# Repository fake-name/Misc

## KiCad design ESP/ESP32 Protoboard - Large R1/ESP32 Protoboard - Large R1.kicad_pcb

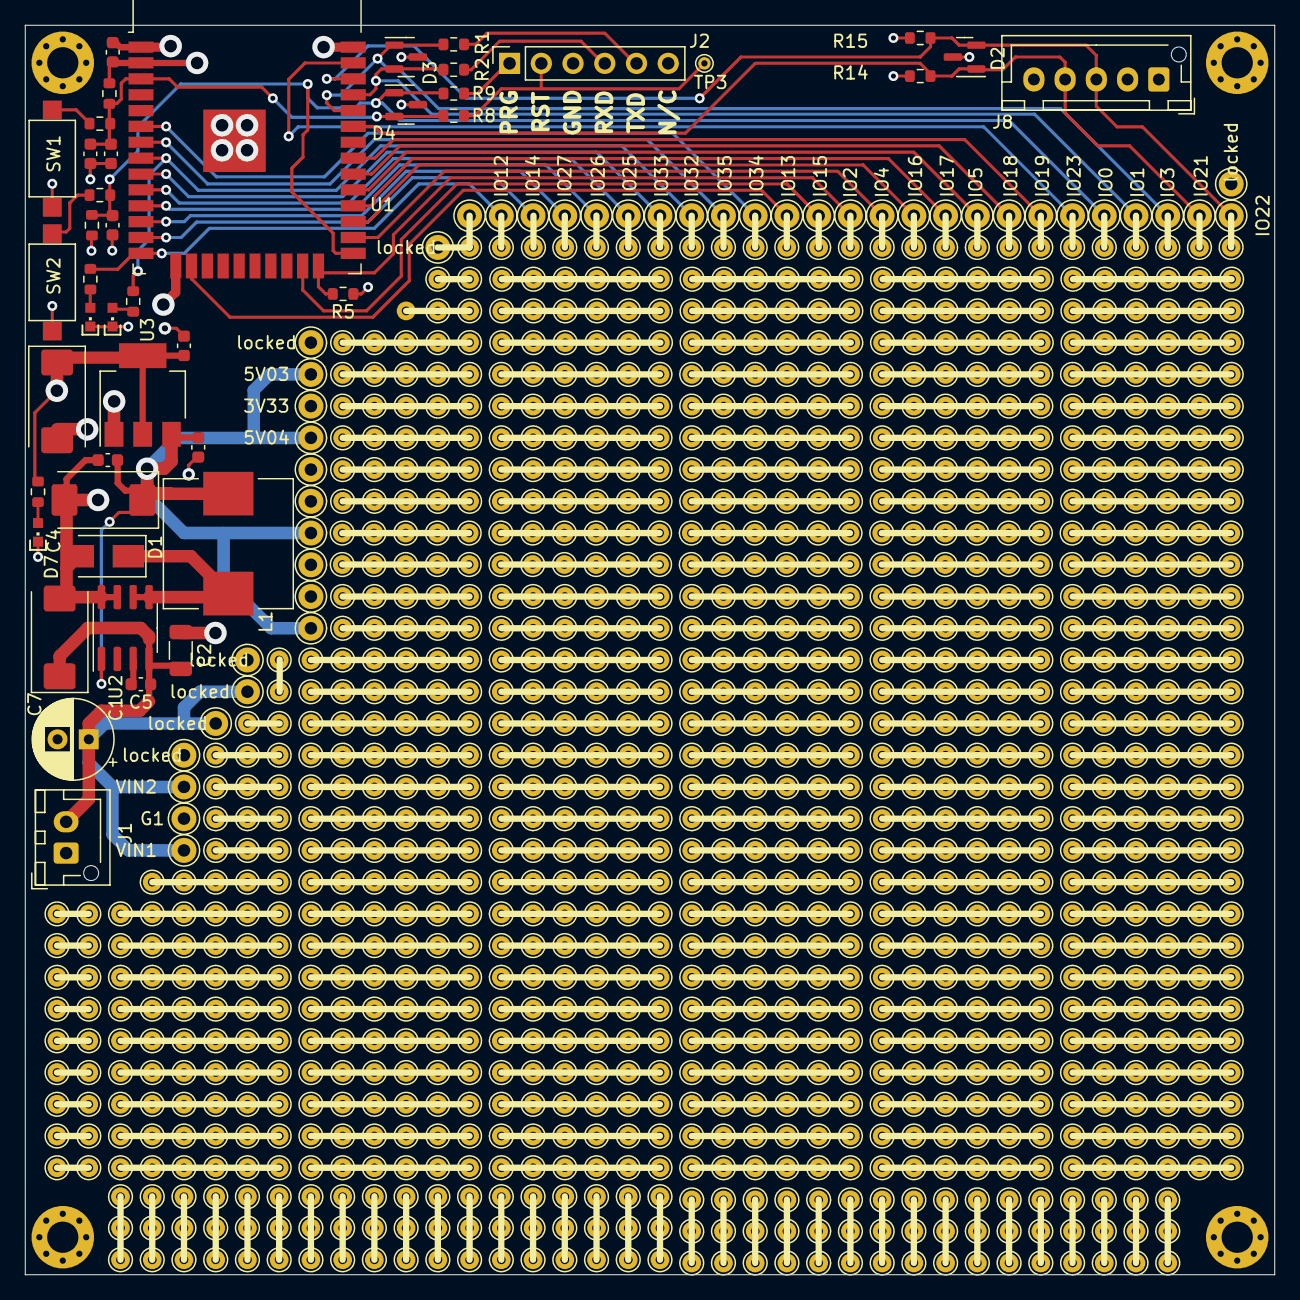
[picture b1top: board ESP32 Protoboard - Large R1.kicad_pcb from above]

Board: 4 copper layers, 100.0 x 100.0 mm, 92 parts (0 on the bottom side), 40 nets.

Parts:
3V33, 5V03, 5V04: TestPoint; Pin_D1.0mm_L10.0mm
C1: 47uF; CP_Radial_D6.3mm_P2.50mm
C2: 1 uF; C_1206_3216Metric
C3, C5, C6, C9, C11: 1 uF; C_0603_1608Metric
C4, C10: 100uF; CP_EIA-7343-20_Kemet-V
C7: 47uF; CP_EIA-7343-20_Kemet-V
C8: 0.1 uF; C_0603_1608Metric
C12, C13: DNP; C_0603_1608Metric
D1: SS36; D_SMA
D2, D3, D4: BAT54C; SOT-23
D7, D8, D12: LED; CHIPLED_0603
G1, G6: TestPoint; Pin_D1.0mm_L10.0mm
H1, H2, H3, H4: MountingHole; MountingHole_2.5mm_Pad_Via
IO0, IO1, IO2, IO3, IO4, IO5, IO12, IO13, IO14, IO15, IO16, IO17, IO18, IO19, IO21, IO22, IO23, IO25, IO26, IO27, IO32, IO33, IO34, IO35: TestPoint; Pin_D1.0mm_L10.0mm
J1: Conn_01x02; JST_XH_B2B-XH-AM_1x02_P2.50mm_Vertical
J2: Conn_01x06; PinSocket_1x06_P2.54mm_Vertical
J8: Conn_01x05; JST_XH_B5B-XH-AM_1x05_P2.50mm_Vertical
L1: 47uH/3A; L_Wuerth_HCI-1040
R1, R2, R3, R7, R8, R9, R10, R26, R27: 470R; R_0603_1608Metric
R4: 10K; R_0603_1608Metric
R5, R6, R14, R15: 4.7K; R_0603_1608Metric
SW1, SW2: SW_Push; SW_SPST_CK_RS282G05A3
TP3: TestPoint; TestPoint_THTPad_D1.0mm_Drill0.5mm
U1: ESP32-WROOM-32D; ESP32-WROOM-32
U2: XL2001; SOIC-8_3.9x4.9mm_P1.27mm
U3: AMS1117-3.3; SOT-223-3_TabPin2
VIN1, VIN2: TestPoint; Pin_D1.0mm_L10.0mm
locked: TestPoint; Pin_D1.0mm_L10.0mm
locked#2, locked#3, locked#4, locked#5, locked#6, locked#7, locked#8, locked#9, locked#10, locked#11, locked#12, locked#13: TestPoint; Pin_D1.0mm_L10.0mm

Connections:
+3V3: 3V33.1, C9.1, C10.1, C11.1, D2.3 (A), D3.3 (A), D4.3 (A), J8.2, R4.2, R6.2, R14.2, R15.2, R26.2, U1.2 (VDD), U3.2 (VO), locked#2.1, locked#10.1, locked#12.1
+5V: 5V03.1, 5V04.1, C3.1, C4.1, C6.1, J8.1, L1.2, U2.1 (FB), U3.3 (VI), locked#3.1, locked#13.1
/PROG: C13.1, D4.1 (K), IO0.1, R6.1, R7.2, R9.1, U1.25 (IO0)
/RESET: C8.1, C12.1, D4.2 (K), R3.2, R4.1, R8.1, U1.3 (EN)
/RXD: D3.2 (K), IO1.1, R2.1, U1.35 (TXD0/IO1)
/TXD: D3.1 (K), IO3.1, R1.1, U1.34 (RXD0/IO3)
GND: C1.2, C2.2, C3.2, C4.2, C6.2, C7.2, C8.2, C9.2, C10.2, C11.2, C12.2, C13.2, D1.2 (A), D7.1 (K), D8.1 (K), D12.1 (K), G1.1, G6.1, J1.1, J2.3, J8.5, R5.1, SW1.2, SW2.2, U1.1 (GND), U1.15 (GND), U1.38 (GND), U1.39 (GND), U2.7 (GND), U2.8 (GND), U3.1 (GND), locked#4.1, locked#5.1, locked#6.1, locked#7.1, locked#9.1, locked#11.1
unnamed: C5.2, U2.3 (VC)
unnamed: D1.1 (K), L1.1, U2.5 (SW), U2.6 (SW)
unnamed: D2.1 (K), IO21.1, J8.4, R14.1, U1.33 (IO21)
unnamed: D2.2 (K), IO22.1, J8.3, R15.1, U1.36 (IO22)
unnamed: D7.2 (A), R26.1
unnamed: D8.2 (A), R27.1
unnamed: D12.2 (A), R10.1
unnamed: IO2.1, R5.2, U1.24 (IO2)
unnamed: IO4.1, U1.26 (IO4)
unnamed: IO5.1, U1.29 (IO5)
unnamed: IO12.1, R10.2, U1.14 (IO12)
unnamed: IO13.1, U1.16 (IO13)
unnamed: IO14.1, U1.13 (IO14)
unnamed: IO15.1, U1.23 (IO15)
unnamed: IO16.1, U1.27 (IO16)
unnamed: IO17.1, U1.28 (IO17)
unnamed: IO18.1, U1.30 (IO18)
unnamed: IO19.1, U1.31 (IO19)
unnamed: IO23.1, U1.37 (IO23)
unnamed: IO25.1, U1.10 (IO25)
unnamed: IO26.1, U1.11 (IO26)
unnamed: IO27.1, U1.12 (IO27)
unnamed: IO32.1, R27.2, U1.8 (IO32)
unnamed: IO33.1, U1.9 (IO33)
unnamed: IO34.1, U1.6 (IO34)
unnamed: IO35.1, U1.7 (IO35)
unnamed: J2.1, R9.2
unnamed: J2.2, R8.2, TP3.1
unnamed: J2.4, R2.2
unnamed: J2.5, R1.2
unnamed: R3.1, SW1.1
unnamed: R7.1, SW2.1
VCC: C1.1, C2.1, C5.1, C7.1, J1.2, U2.4 (VIn), VIN1.1, VIN2.1, locked.1, locked#8.1

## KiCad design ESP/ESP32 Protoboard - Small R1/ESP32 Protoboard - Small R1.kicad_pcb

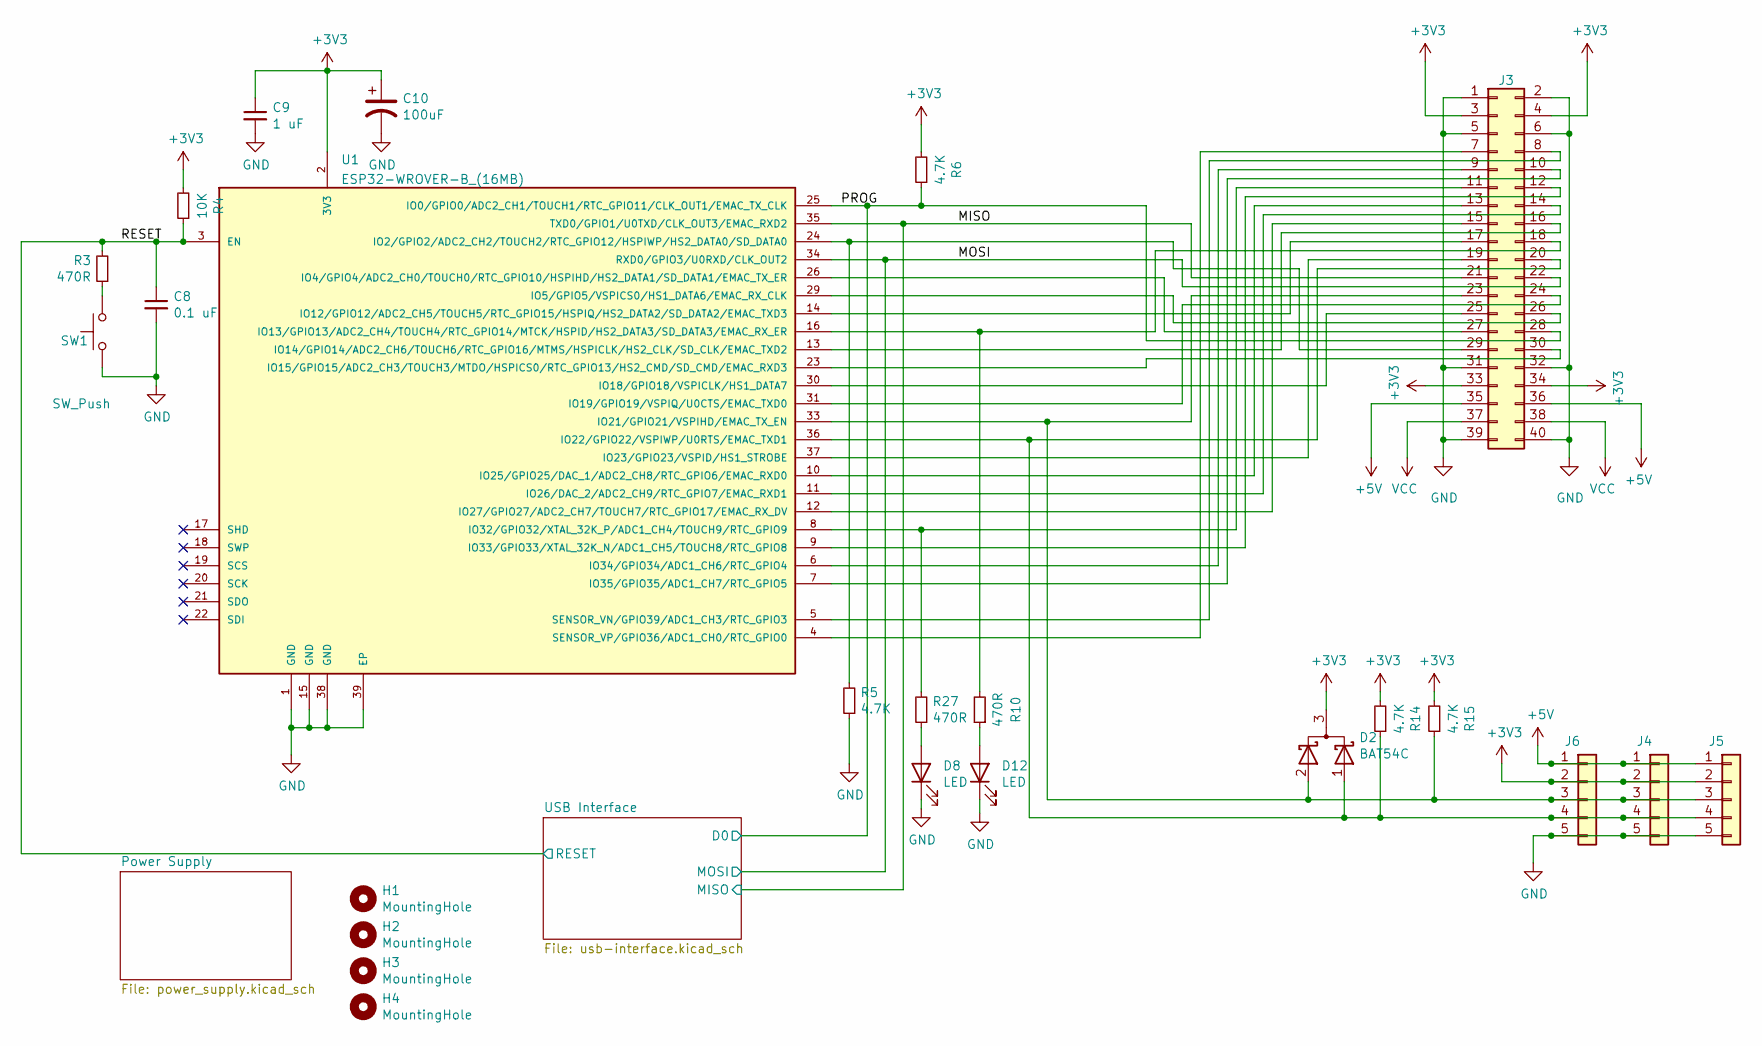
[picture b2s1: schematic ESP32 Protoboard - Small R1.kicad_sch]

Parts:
C8: 0.1 uF; C_0603_1608Metric; LCSC C15849
C9: 1 uF; C_0603_1608Metric; LCSC C14663
C10: 100uF; CP_EIA-7343-20_Kemet-V; LCSC C14663
D2: BAT54C; SOT-23; LCSC C14663
D8, D12: LED; CHIPLED_0603; LCSC C14663
H1, H2, H3, H4: MountingHole; MountingHole_2.5mm_Pad_Via
J3: Conn_02x20_Top_Bottom; PinHeader_2x20_P2.54mm_Vertical
J4, J5, J6: Conn_01x05; JST_XH_B5B-XH-AM_1x05_P2.50mm_Vertical; LCSC C14663
R3, R10, R27: 470R; R_0603_1608Metric; LCSC C14663
R4: 10K; R_0603_1608Metric; LCSC C14663
R5, R6, R14, R15: 4.7K; R_0603_1608Metric; LCSC C14663
SW1: SW_Push; SW_SPST_CK_RS282G05A3; LCSC C14663
U1: ESP32-WROVER-B_(16MB); XCVR_ESP32-WROVER-B_(16MB); PARTREV 1.1

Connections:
+3V3: C9.1, C10.1, D2.3 (A), J3.3, J3.4, J3.33, J3.34, J4.2, J5.2, J6.2, R4.2, R6.2, R14.2, R15.2, U1.2 (3V3); also elsewhere on the board
+5V: J3.35, J3.36, J4.1, J5.1, J6.1; also elsewhere on the board
/MISO: J3.21, U1.35 (TXD0/GPIO1/U0TXD/CLK_OUT3/EMAC_RXD2); also elsewhere on the board
/MOSI: J3.22, U1.34 (RXD0/GPIO3/U0RXD/CLK_OUT2); also elsewhere on the board
/PROG: J3.28, R6.1, U1.25 (IO0/GPIO0/ADC2_CH1/TOUCH1/RTC_GPIO11/CL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); also elsewhere on the board
/RESET: C8.1, R3.2, R4.1, U1.3 (EN); also elsewhere on the board
GND: C8.2, C9.2, C10.2, D8.1 (K), D12.1 (K), J3.1, J3.2, J3.5, J3.6, J3.31, J3.32, J3.39, J3.40, J4.5, J5.5, J6.5, R5.1, SW1.2, U1.1 (GND), U1.15 (GND), U1.38 (GND), U1.39 (EP); also elsewhere on the board
unnamed: D2.1 (K), J3.20, J4.4, J5.4, J6.4, R14.1, U1.36 (IO22/GPIO22/VSPIWP/U0RTS/EMAC_TXD1)
unnamed: D2.2 (K), J3.23, J4.3, J5.3, J6.3, R15.1, U1.33 (IO21/GPIO21/VSPIHD/EMAC_TX_EN)
unnamed: D8.2 (A), R27.1
unnamed: D12.2 (A), R10.1
unnamed: J3.7, U1.4 (SENSOR_VP/GPIO36/ADC1_CH0/RTC_GPIO0)
unnamed: J3.8, U1.5 (SENSOR_VN/GPIO39/ADC1_CH3/RTC_GPIO3)
unnamed: J3.9, U1.6 (IO34/GPIO34/ADC1_CH6/RTC_GPIO4)
unnamed: J3.10, U1.7 (IO35/GPIO35/ADC1_CH7/RTC_GPIO5)
unnamed: J3.11, R27.2, U1.8 (IO32/GPIO32/XTAL_32K_P/ADC1_CH4/TOUCH9/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)
unnamed: J3.12, U1.9 (IO33/GPIO33/XTAL_32K_N/ADC1_CH5/TOUCH8/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)
unnamed: J3.13, U1.10 (IO25/GPIO25/DAC_1/ADC2_CH8/RTC_GPIO6/EM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)
unnamed: J3.14, U1.11 (IO26/DAC_2/ADC2_CH9/RTC_GPIO7/EMAC_RXD1)
unnamed: J3.15, U1.12 (IO27/GPIO27/ADC2_CH7/TOUCH7/RTC_GPIO17/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)
unnamed: J3.16, U1.13 (IO14/GPIO14/ADC2_CH6/TOUCH6/RTC_GPIO16/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)
unnamed: J3.17, U1.14 (IO12/GPIO12/ADC2_CH5/TOUCH5/RTC_GPIO15/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)
unnamed: J3.18, R10.2, U1.16 (IO13/GPIO13/ADC2_CH4/TOUCH4/RTC_GPIO14/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)
unnamed: J3.19, U1.37 (IO23/GPIO23/VSPID/HS1_STROBE)
unnamed: J3.24, U1.31 (IO19/GPIO19/VSPIQ/U0CTS/EMAC_TXD0)
unnamed: J3.25, U1.30 (IO18/GPIO18/VSPICLK/HS1_DATA7)
unnamed: J3.26, U1.29 (IO5/GPIO5/VSPICS0/HS1_DATA6/EMAC_RX_CLK)
unnamed: J3.27, U1.26 (IO4/GPIO4/ADC2_CH0/TOUCH0/RTC_GPIO10/HS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)
unnamed: J3.29, R5.2, U1.24 (IO2/GPIO2/ADC2_CH2/TOUCH2/RTC_GPIO12/HS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)
unnamed: J3.30, U1.23 (IO15/GPIO15/ADC2_CH3/TOUCH3/MTDO/HSPICS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)
unnamed: R3.1, SW1.1
VCC: J3.37, J3.38; also elsewhere on the board

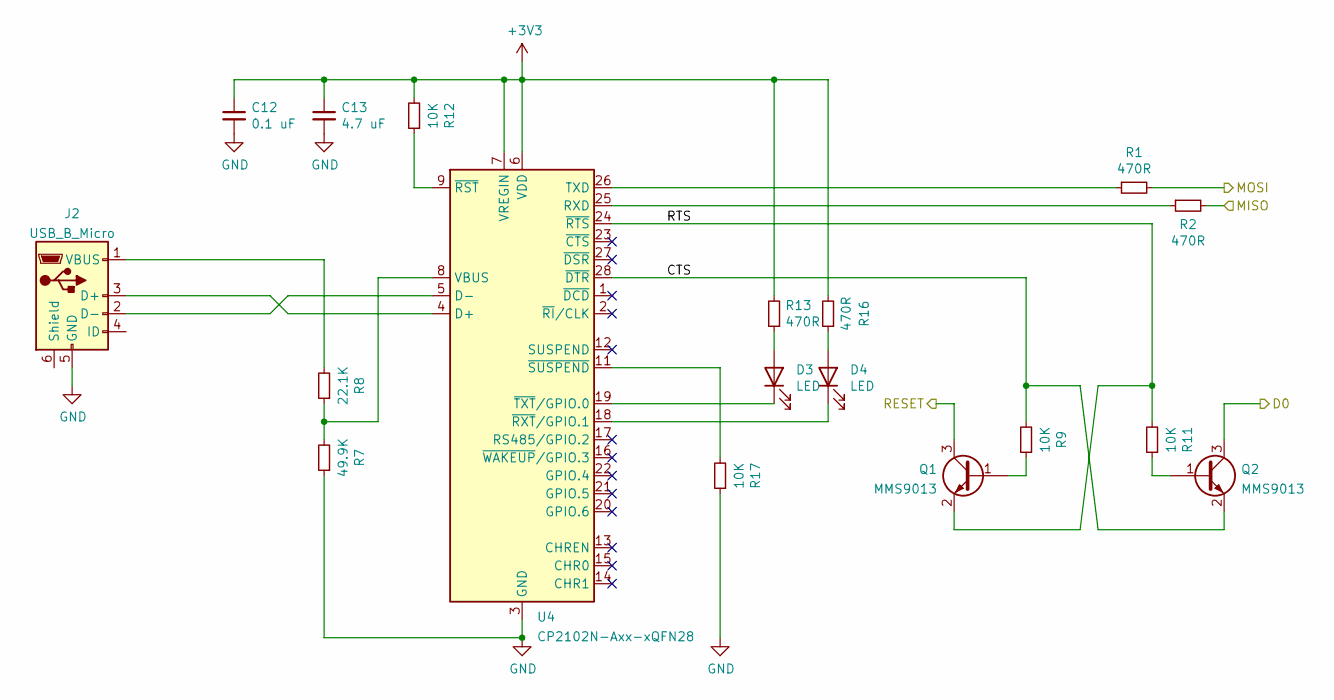
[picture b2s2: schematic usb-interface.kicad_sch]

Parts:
C12: 0.1 uF; C_0603_1608Metric; LCSC C14663
C13: 4.7 uF; C_0603_1608Metric; LCSC C19666
D3, D4: LED; CHIPLED_0603; LCSC C14663
J2: USB_B_Micro; Molex--0-0-0
Q1, Q2: MMS9013; SOT-23; LCSC MMS9013
R1, R2, R13, R16: 470R; R_0603_1608Metric; LCSC C14663
R7: 49.9K; R_0603_1608Metric; LCSC C23184
R8: 22.1K; R_0603_1608Metric; LCSC C23184
R9, R11, R12, R17: 10K; R_0603_1608Metric; LCSC C25804
U4: CP2102N-Axx-xQFN28; QFN-28-1EP_5x5mm_P0.5mm_EP3.35x3.35mm

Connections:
+3V3: C12.1, C13.1, R12.2, R13.2, R16.2, U4.6 (VDD), U4.7 (VREGIN); also elsewhere on the board
/MISO: R2.2; also elsewhere on the board
/MOSI: R1.2; also elsewhere on the board
/PROG: Q2.3 (C); also elsewhere on the board
/RESET: Q1.3 (C); also elsewhere on the board
/USB Interface/CTS: Q2.2 (E), R9.2, U4.28 (~DTR)
/USB Interface/RTS: Q1.2 (E), R11.2, U4.24 (~RTS)
GND: C12.2, C13.2, J2.5 (GND), R7.1, R17.1, U4.3 (GND), U4.29 (GND); also elsewhere on the board
unnamed: D3.1 (K), U4.19 (~TXT/GPIO.0)
unnamed: D3.2 (A), R13.1
unnamed: D4.1 (K), U4.18 (~RXT/GPIO.1)
unnamed: D4.2 (A), R16.1
unnamed: J2.1 (VBUS), R8.2
unnamed: J2.2 (D-), U4.5 (D-)
unnamed: J2.3 (D+), U4.4 (D+)
unnamed: Q1.1 (B), R9.1
unnamed: Q2.1 (B), R11.1
unnamed: R1.1, U4.26 (TXD)
unnamed: R2.1, U4.25 (RXD)
unnamed: R7.2, R8.1, U4.8 (VBUS)
unnamed: R12.1, U4.9 (~RST)
unnamed: R17.2, U4.11 (~SUSPEND)

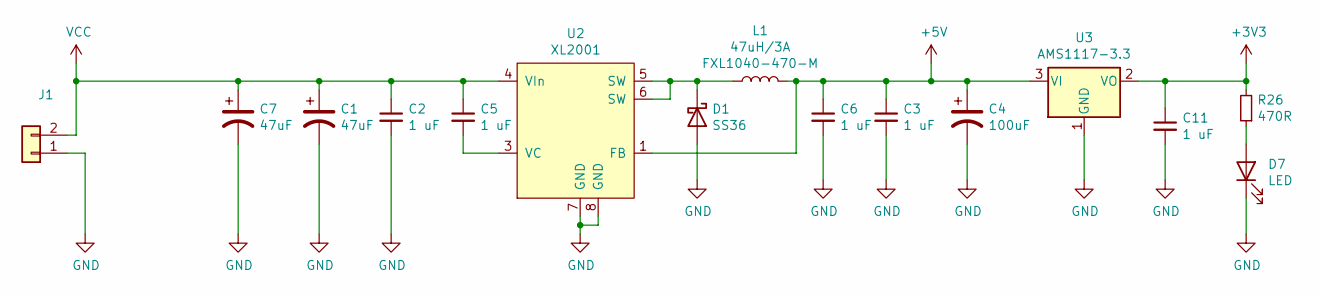
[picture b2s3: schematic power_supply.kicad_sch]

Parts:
C1: 47uF; CP_Radial_D6.3mm_P2.50mm; LCSC C14663
C2: 1 uF; C_1206_3216Metric; LCSC C14663
C3, C5, C6, C11: 1 uF; C_0603_1608Metric; LCSC C14663
C4: 100uF; CP_EIA-7343-20_Kemet-V; LCSC C14663
C7: 47uF; CP_EIA-7343-20_Kemet-V; LCSC C14663
D1: SS36; D_SMA; LCSC C14663
D7: LED; CHIPLED_0603; LCSC C14663
J1: Conn_01x02; JST_XH_B2B-XH-AM_1x02_P2.50mm_Vertical; LCSC C14663
L1: 47uH/3A; L_Wuerth_HCI-1040; LCSC C14663
R26: 470R; R_0603_1608Metric; LCSC C14663
U2: XL2001; SOIC-8_3.9x4.9mm_P1.27mm; LCSC C14663
U3: AMS1117-3.3; SOT-223-3_TabPin2; LCSC C14663

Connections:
+3V3: C11.1, R26.2, U3.2 (VO); also elsewhere on the board
+5V: C3.1, C4.1, C6.1, L1.2, U2.1 (FB), U3.3 (VI); also elsewhere on the board
GND: C1.2, C2.2, C3.2, C4.2, C6.2, C7.2, C11.2, D1.2 (A), D7.1 (K), J1.1, U2.7 (GND), U2.8 (GND), U3.1 (GND); also elsewhere on the board
unnamed: C5.2, U2.3 (VC)
unnamed: D1.1 (K), L1.1, U2.5 (SW), U2.6 (SW)
unnamed: D7.2 (A), R26.1
VCC: C1.1, C2.1, C5.1, C7.1, J1.2, U2.4 (VIn); also elsewhere on the board

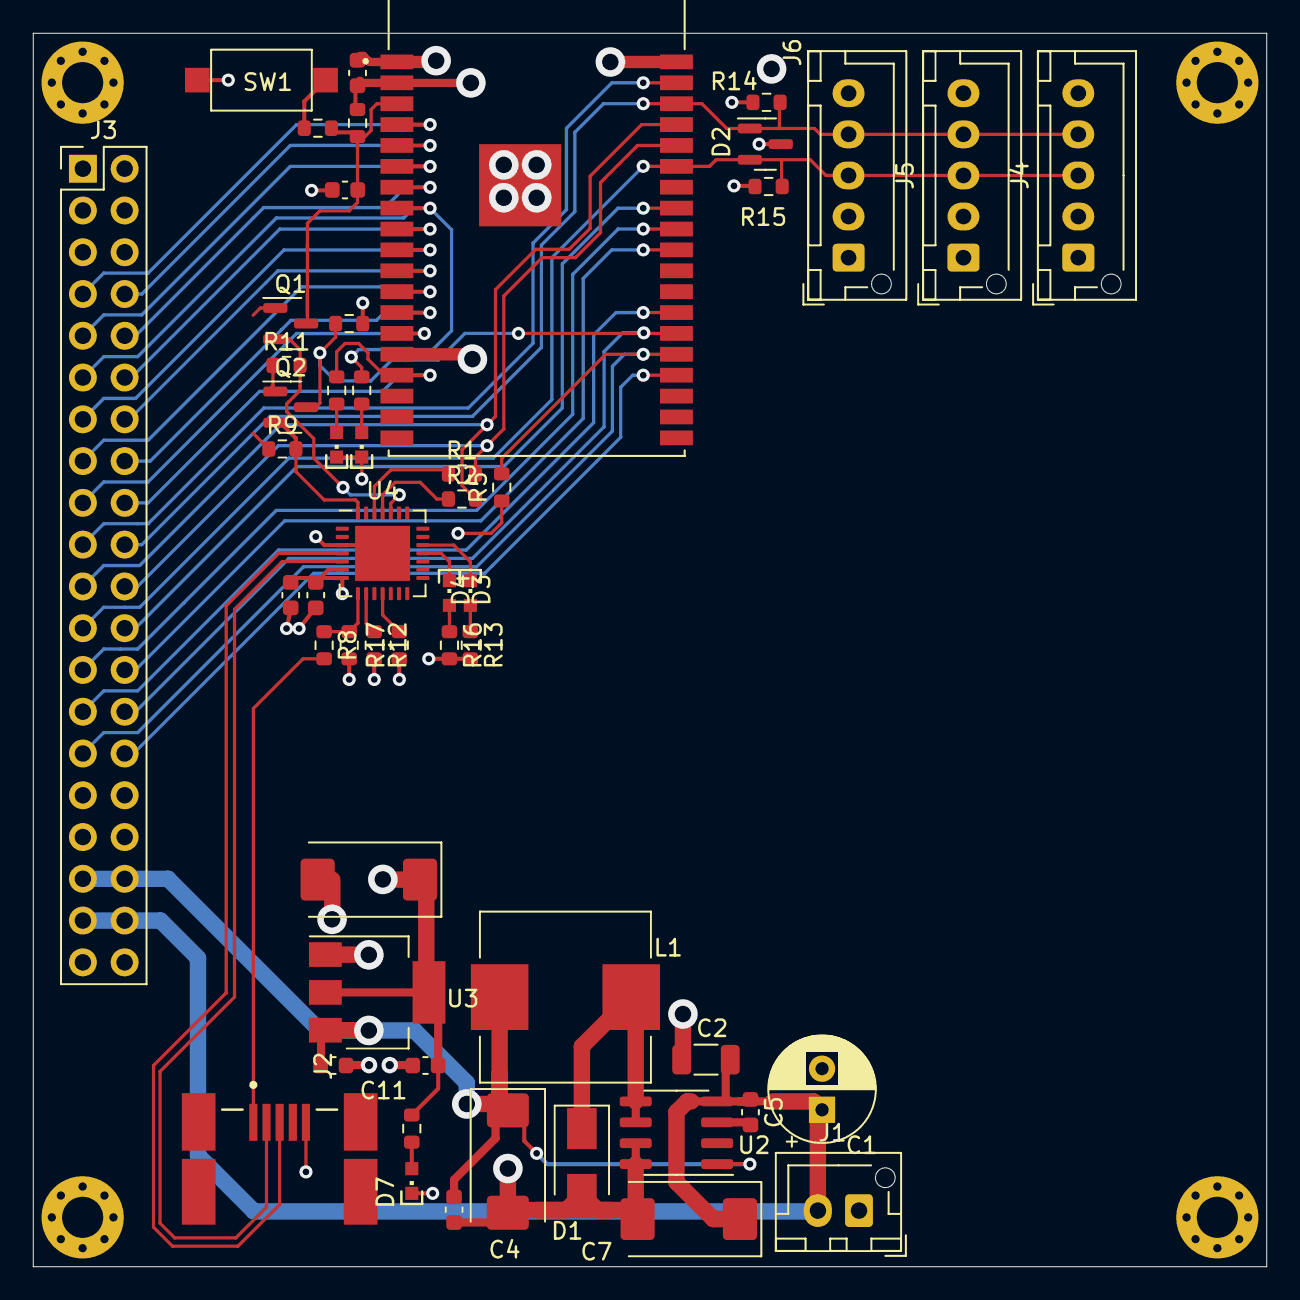
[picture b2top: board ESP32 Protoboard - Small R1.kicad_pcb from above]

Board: 4 copper layers, 75.0 x 75.0 mm, 57 parts (0 on the bottom side), 51 nets.

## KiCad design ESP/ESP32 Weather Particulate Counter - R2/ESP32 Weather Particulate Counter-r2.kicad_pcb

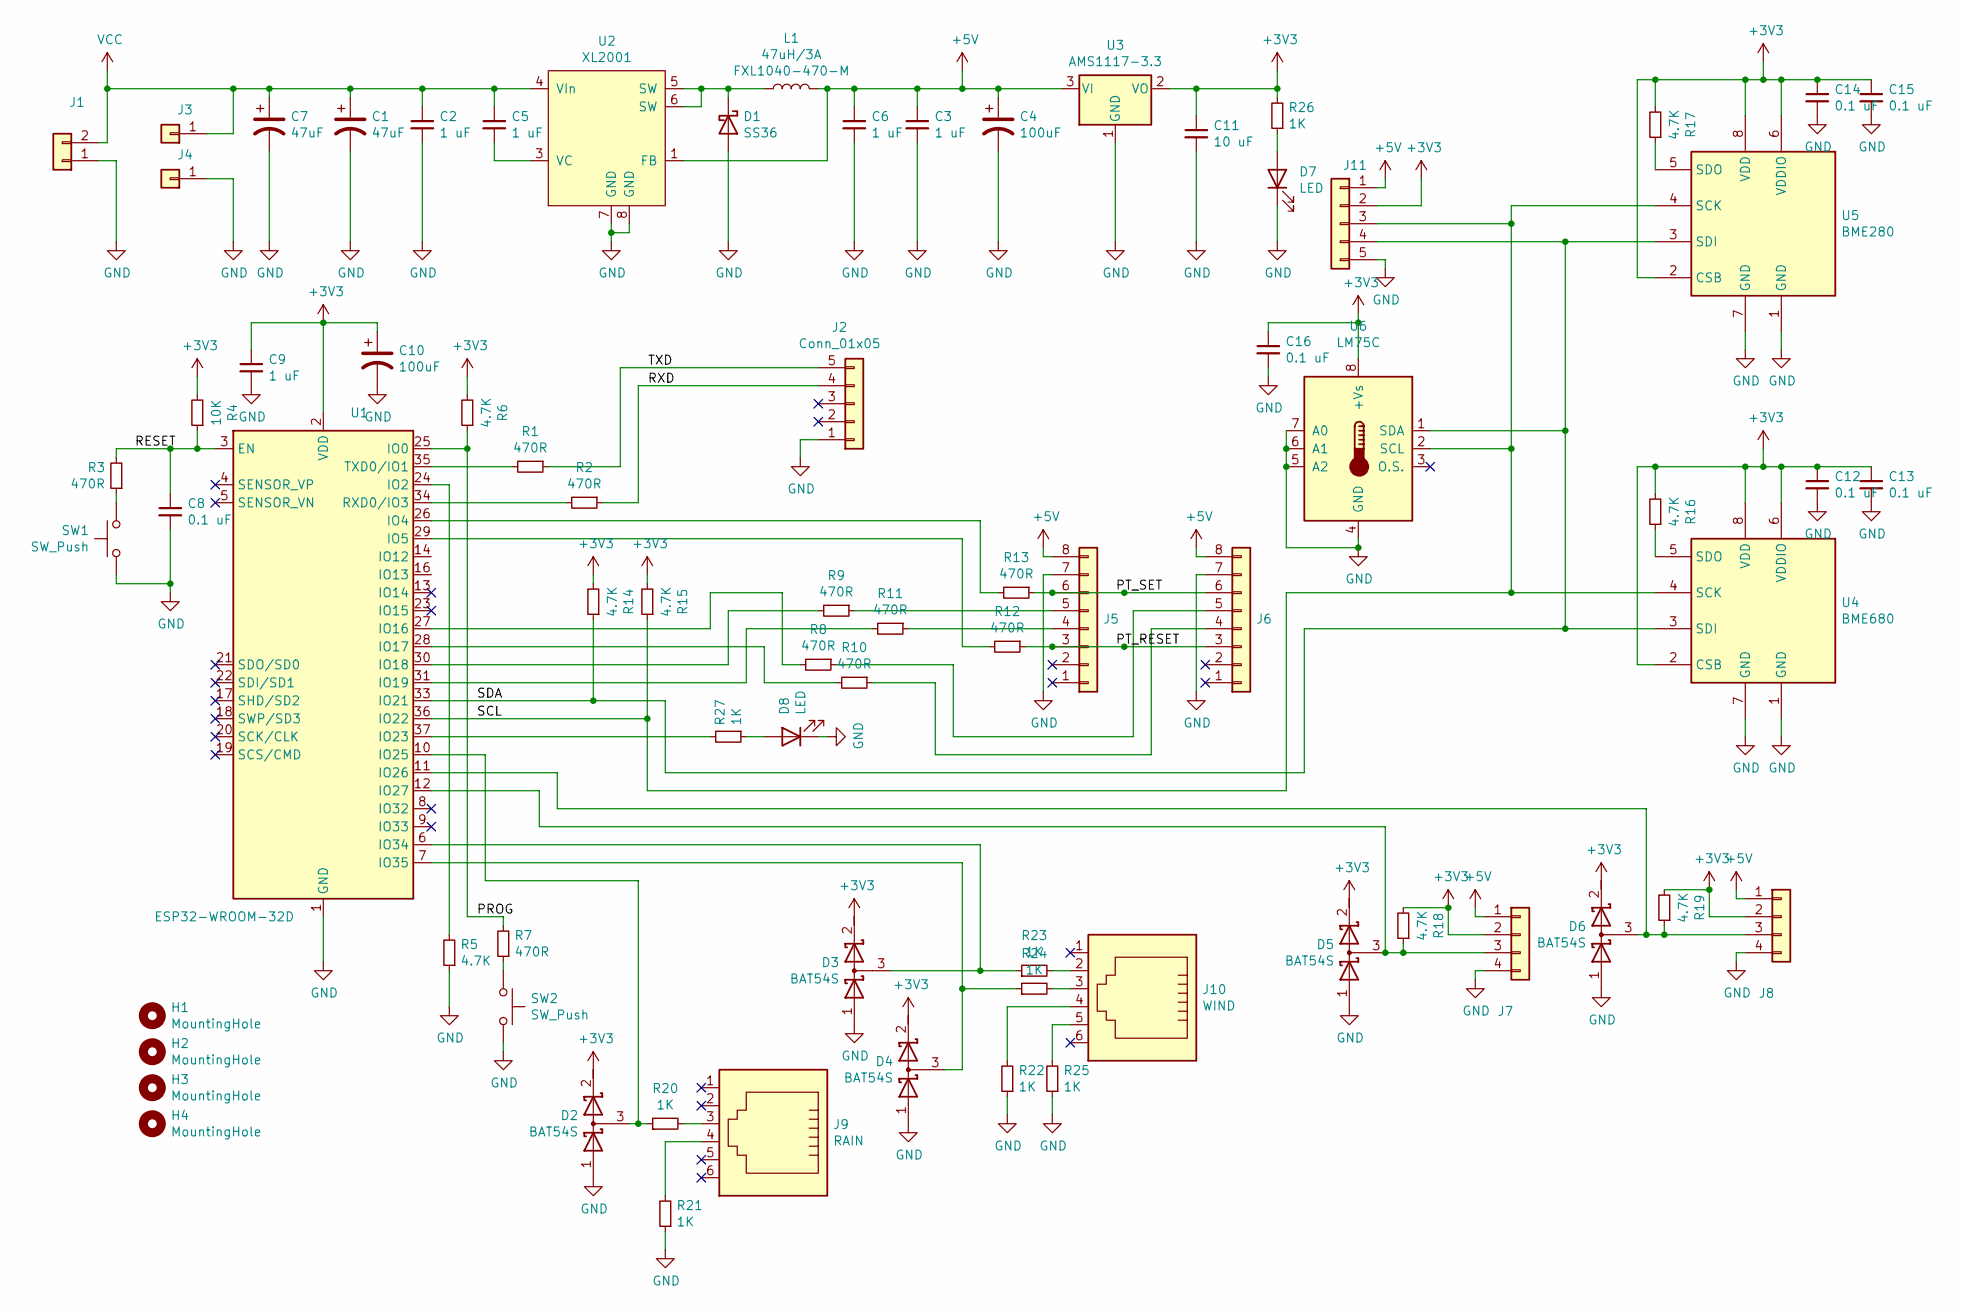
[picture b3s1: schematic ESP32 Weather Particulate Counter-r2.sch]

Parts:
C1: 47uF; CP_Radial_D6.3mm_P2.50mm
C2: 1 uF; C_1206_3216Metric_Pad1.42x1.75mm_HandSolder
C3, C5, C6, C9: 1 uF; C_0603_1608Metric_Pad1.05x0.95mm_HandSolder
C4, C10: 100uF; CP_EIA-7343-20_Kemet-V_Pad2.25x2.55mm_HandSolder
C7: 47uF; CP_EIA-7343-20_Kemet-V_Pad2.25x2.55mm_HandSolder
C8, C12, C13, C14, C15, C16: 0.1 uF; C_0603_1608Metric_Pad1.05x0.95mm_HandSolder
C11: 10 uF; C_0603_1608Metric_Pad1.05x0.95mm_HandSolder
D1: SS36; D_SMA_Handsoldering
D2, D3, D4, D5, D6: BAT54S; SOT-23
D7, D8: LED; CHIPLED_0603
H1, H2, H3, H4: MountingHole; MountingHole_2.5mm_Pad_Via
J1: Conn_01x02; PinHeader_1x02_P2.54mm_Vertical
J2: Conn_01x05; PinHeader_1x05_P2.54mm_Vertical
J3, J4: Conn_01x01; Pin_D1.3mm_L11.0mm
J5, J6: Conn_01x08; Molex_PicoBlade_53047-0810_1x08_P1.25mm_Vertical
J7, J8: Conn_01x04; JST_XH_B4B-XH-AM_1x04_P2.50mm_Vertical
J9: RAIN; RJ25_Wayconn_MJEA-660X1_Horizontal
J10: WIND; RJ25_Wayconn_MJEA-660X1_Horizontal
J11: Conn_01x05; JST_XH_B5B-XH-AM_1x05_P2.50mm_Vertical
L1: 47uH/3A; L_Wuerth_HCI-1040
R1, R2, R3, R7, R8, R9, R10, R11, R12, R13: 470R; R_0603_1608Metric_Pad1.05x0.95mm_HandSolder
R4: 10K; R_0603_1608Metric_Pad1.05x0.95mm_HandSolder
R5, R6, R14, R15, R16, R17, R18, R19: 4.7K; R_0603_1608Metric_Pad1.05x0.95mm_HandSolder
R20, R21, R22, R23, R24, R25, R26, R27: 1K; R_0603_1608Metric_Pad1.05x0.95mm_HandSolder
SW1, SW2: SW_Push; K2-1823SA-A4DW-06
U1: ESP32-WROOM-32D; ESP32-WROOM-32
U2: XL2001; SOIC-8_3.9x4.9mm_P1.27mm
U3: AMS1117-3.3; SOT-223-3_TabPin2
U4: BME680; Bosch_LGA-8_3x3mm_P0.8mm_ClockwisePinNumbering
U5: BME280; Bosch_LGA-8_2.5x2.5mm_P0.65mm_ClockwisePinNumbering
U6: LM75C; MSOP-8_3x3mm_P0.65mm

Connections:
+3V3: C9.1, C10.1, C11.1, C12.1, C13.1, C14.1, C15.1, C16.1, D2.2 (K), D3.2 (K), D4.2 (K), D5.2 (K), D6.2 (K), J7.2, J8.2, J11.2, R4.2, R6.2, R14.2, R15.2, R16.2, R17.2, R18.2, R19.2, R26.2, U1.2 (VDD), U3.2 (VO), U4.2 (CSB), U4.6 (VDDIO), U4.8 (VDD), U5.2 (CSB), U5.6 (VDDIO), U5.8 (VDD), U6.8 (+Vs)
+5V: C3.1, C4.1, C6.1, J5.8, J6.8, J7.1, J8.1, J11.1, L1.2, U2.1 (FB), U3.3 (VI)
/PROG: R6.1, R7.2, U1.25 (IO0)
/PT_RESET: J5.3, J6.3, R12.1
/PT_SET: J5.6, J6.6, R13.1
/RESET: C8.1, R3.2, R4.1, U1.3 (EN)
/RXD: J2.4, R2.1
/SCL: J11.3, R15.1, U1.36 (IO22), U4.4 (SCK), U5.4 (SCK), U6.2 (SCL)
/SDA: J11.4, R14.1, U1.33 (IO21), U4.3 (SDI), U5.3 (SDI), U6.1 (SDA)
/TXD: J2.5, R1.1
GND: C1.2, C2.2, C3.2, C4.2, C6.2, C7.2, C8.2, C9.2, C10.2, C11.2, C12.2, C13.2, C14.2, C15.2, C16.2, D1.2 (A), D2.1 (A), D3.1 (A), D4.1 (A), D5.1 (A), D6.1 (A), D7.1 (K), D8.1 (K), J1.1, J2.1, J4.1, J5.7, J6.7, J7.4, J8.4, J11.5, R5.1, R21.1, R22.1, R25.1, SW1.2, SW2.2, U1.1 (GND), U1.15 (GND), U1.38 (GND), U1.39 (GND), U2.7 (GND), U2.8 (GND), U3.1 (GND), U4.1 (GND), U4.7 (GND), U5.1 (GND), U5.7 (GND), U6.4 (GND), U6.5 (A2), U6.6 (A1), U6.7 (A0)
unnamed: C5.2, U2.3 (VC)
unnamed: D1.1 (K), L1.1, U2.5 (SW), U2.6 (SW)
unnamed: D2.3 (common), R20.1, U1.10 (IO25)
unnamed: D3.3 (common), R23.1, U1.6 (IO34)
unnamed: D4.3 (common), R24.1, U1.7 (IO35)
unnamed: D5.3 (common), J7.3, R18.1, U1.12 (IO27)
unnamed: D6.3 (common), J8.3, R19.1, U1.11 (IO26)
unnamed: D7.2 (A), R26.1
unnamed: D8.2 (A), R27.1
unnamed: J5.4, R11.1
unnamed: J5.5, R9.1
unnamed: J6.4, R10.1
unnamed: J6.5, R8.1
unnamed: J9.3, R20.2
unnamed: J9.4, R21.2
unnamed: J10.2, R23.2
unnamed: J10.3, R24.2
unnamed: J10.4, R22.2
unnamed: J10.5, R25.2
unnamed: R1.2, U1.35 (TXD0/IO1)
unnamed: R2.2, U1.34 (RXD0/IO3)
unnamed: R3.1, SW1.1
unnamed: R5.2, U1.24 (IO2)
unnamed: R7.1, SW2.1
unnamed: R8.2, U1.27 (IO16)
unnamed: R9.2, U1.30 (IO18)
unnamed: R10.2, U1.28 (IO17)
unnamed: R11.2, U1.31 (IO19)
unnamed: R12.2, U1.29 (IO5)
unnamed: R13.2, U1.26 (IO4)
unnamed: R16.1, U4.5 (SDO)
unnamed: R17.1, U5.5 (SDO)
unnamed: R27.2, U1.37 (IO23)
VCC: C1.1, C2.1, C5.1, C7.1, J1.2, J3.1, U2.4 (VIn)

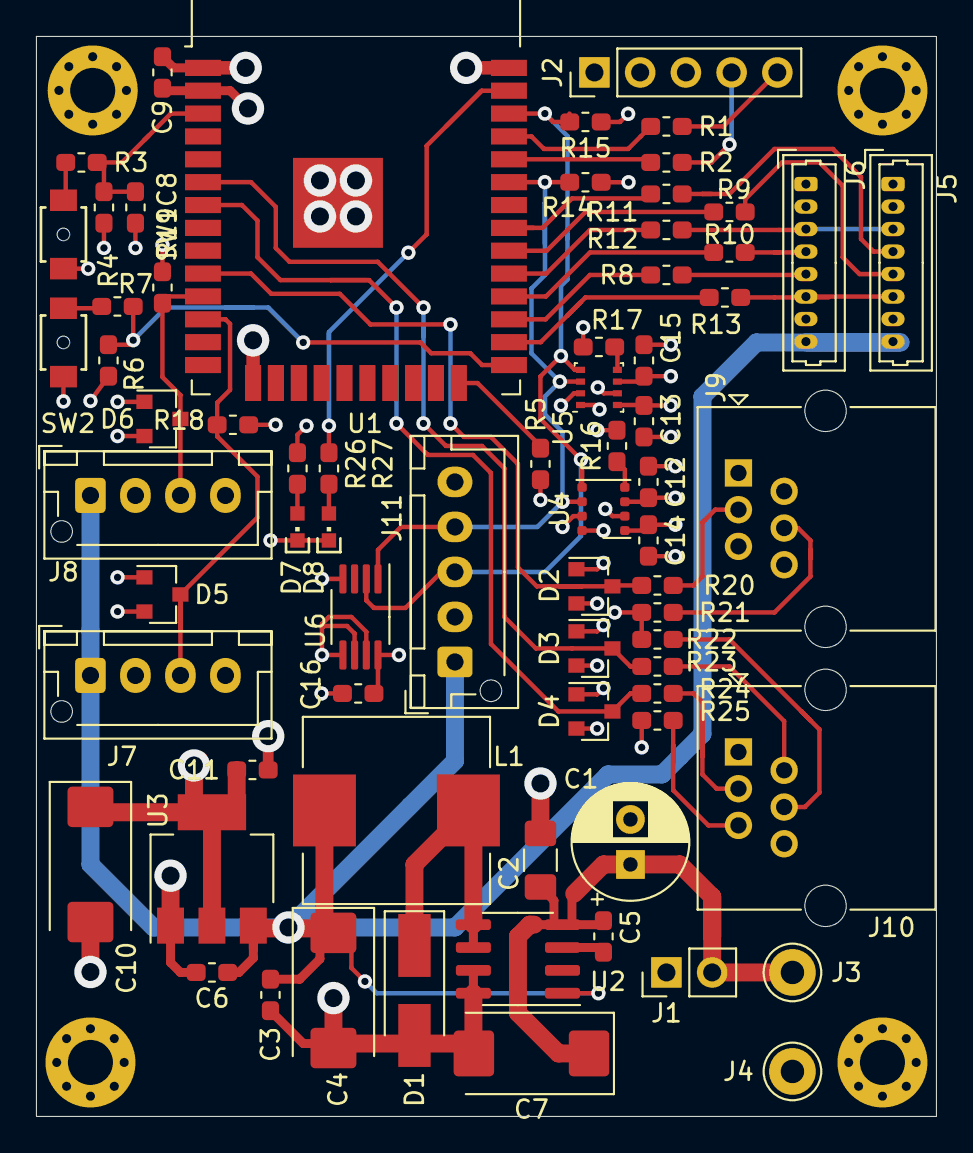
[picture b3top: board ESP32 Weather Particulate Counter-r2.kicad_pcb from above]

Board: 4 copper layers, 50.0 x 60.0 mm, 75 parts (0 on the bottom side), 45 nets.

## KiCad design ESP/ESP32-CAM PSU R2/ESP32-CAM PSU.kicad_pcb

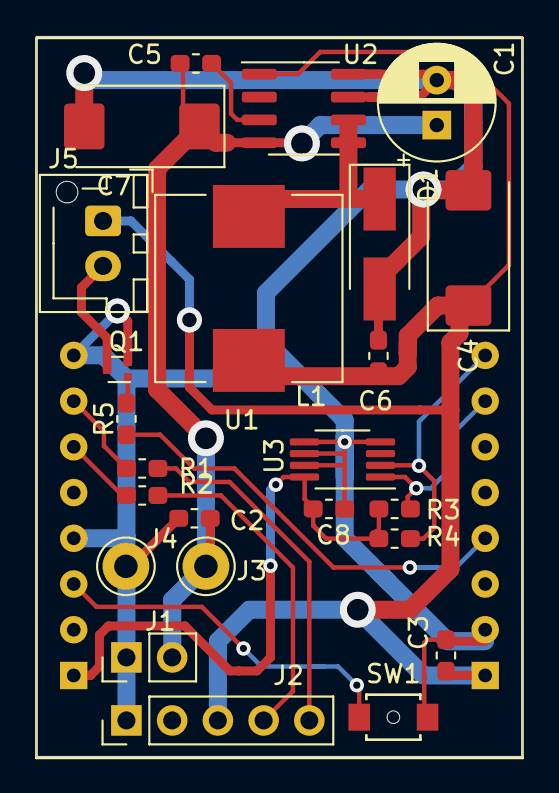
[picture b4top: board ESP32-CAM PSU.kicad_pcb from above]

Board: 2 copper layers, 27.0 x 40.0 mm, 25 parts (0 on the bottom side), 16 nets.

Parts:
C1: 47uF; CP_Radial_D6.3mm_P2.50mm
C2, C3, C5, C6: 1 uF; C_0603_1608Metric_Pad1.05x0.95mm_HandSolder
C4: 100uF; CP_EIA-7343-20_Kemet-V_Pad2.25x2.55mm_HandSolder
C7: 47uF; CP_EIA-7343-20_Kemet-V_Pad2.25x2.55mm_HandSolder
C8: 0.1 uF; C_0603_1608Metric_Pad1.05x0.95mm_HandSolder
D1: SS36; D_SMA_Handsoldering
J1: Conn_01x02; PinHeader_1x02_P2.54mm_Vertical
J2: Conn_01x05; PinHeader_1x05_P2.54mm_Vertical
J3, J4: Conn_01x01; Pin_D1.3mm_L11.0mm
J5: Conn_01x02; JST_XH_B2B-XH-AM_1x02_P2.50mm_Vertical
L1: 47uH/3A; L_Wuerth_HCI-1040
Q1: RUM002N05T2LCT-ND; SOT-723
R1, R2: 470R; R_0603_1608Metric_Pad1.05x0.95mm_HandSolder
R3, R4: 4.7K; R_0603_1608Metric_Pad1.05x0.95mm_HandSolder
R5: 1K; R_0603_1608Metric_Pad1.05x0.95mm_HandSolder
SW1: SW_Push; K2-1823SA-A4DW-06
U1: ESP32-CAM
U2: XL2001; SOIC-8_3.9x4.9mm_P1.27mm
U3: LM75B; MSOP-8_3x3mm_P0.65mm

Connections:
+3V3: C8.1, R3.2, R4.2, U1.16, U3.8
+5V: C3.1, C4.1, C6.1, J2.3, J5.1, L1.2, U1.1, U2.1
/PROG: SW1.1, U1.14
/RXD: J2.4, R2.1
/TXD: J2.5, R1.1
GND: C1.2, C2.2, C3.2, C4.2, C6.2, C7.2, C8.2, D1.2, J1.1, J2.1, J4.1, Q1.2, SW1.2, U1.2, U1.9, U1.13, U2.7, U2.8, U3.4, U3.5, U3.6, U3.7
unnamed: C5.2, U2.3
unnamed: D1.1, L1.1, U2.5, U2.6
unnamed: J5.2, Q1.3
unnamed: Q1.1, R5.2
unnamed: R1.2, U1.10
unnamed: R2.2, U1.11
unnamed: R3.1, U1.7, U3.1
unnamed: R4.1, U1.8, U3.2
unnamed: R5.1, U1.4
VCC: C1.1, C2.1, C5.1, C7.1, J1.2, J3.1, U2.4
